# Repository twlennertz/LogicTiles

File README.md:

<h2>Digital Logic Tile Board Project</h2>

Spring 2017 Senior Project

Cal Poly CPE Department

Authors: Tristan Lennertz & Andrew Wheeler

Implemented for the MSP430 Family

<h3>Please see Project Report for detailed information on this project</h3>

main: The main state machine loop, inits, terminal interface and commands, and ISRs

tiles: Pertains to addressing, selecting, reading, and determining the types of the tiles on the board

graph: Involves the creation and traversal of the graph that underlies and represents the digital circuit

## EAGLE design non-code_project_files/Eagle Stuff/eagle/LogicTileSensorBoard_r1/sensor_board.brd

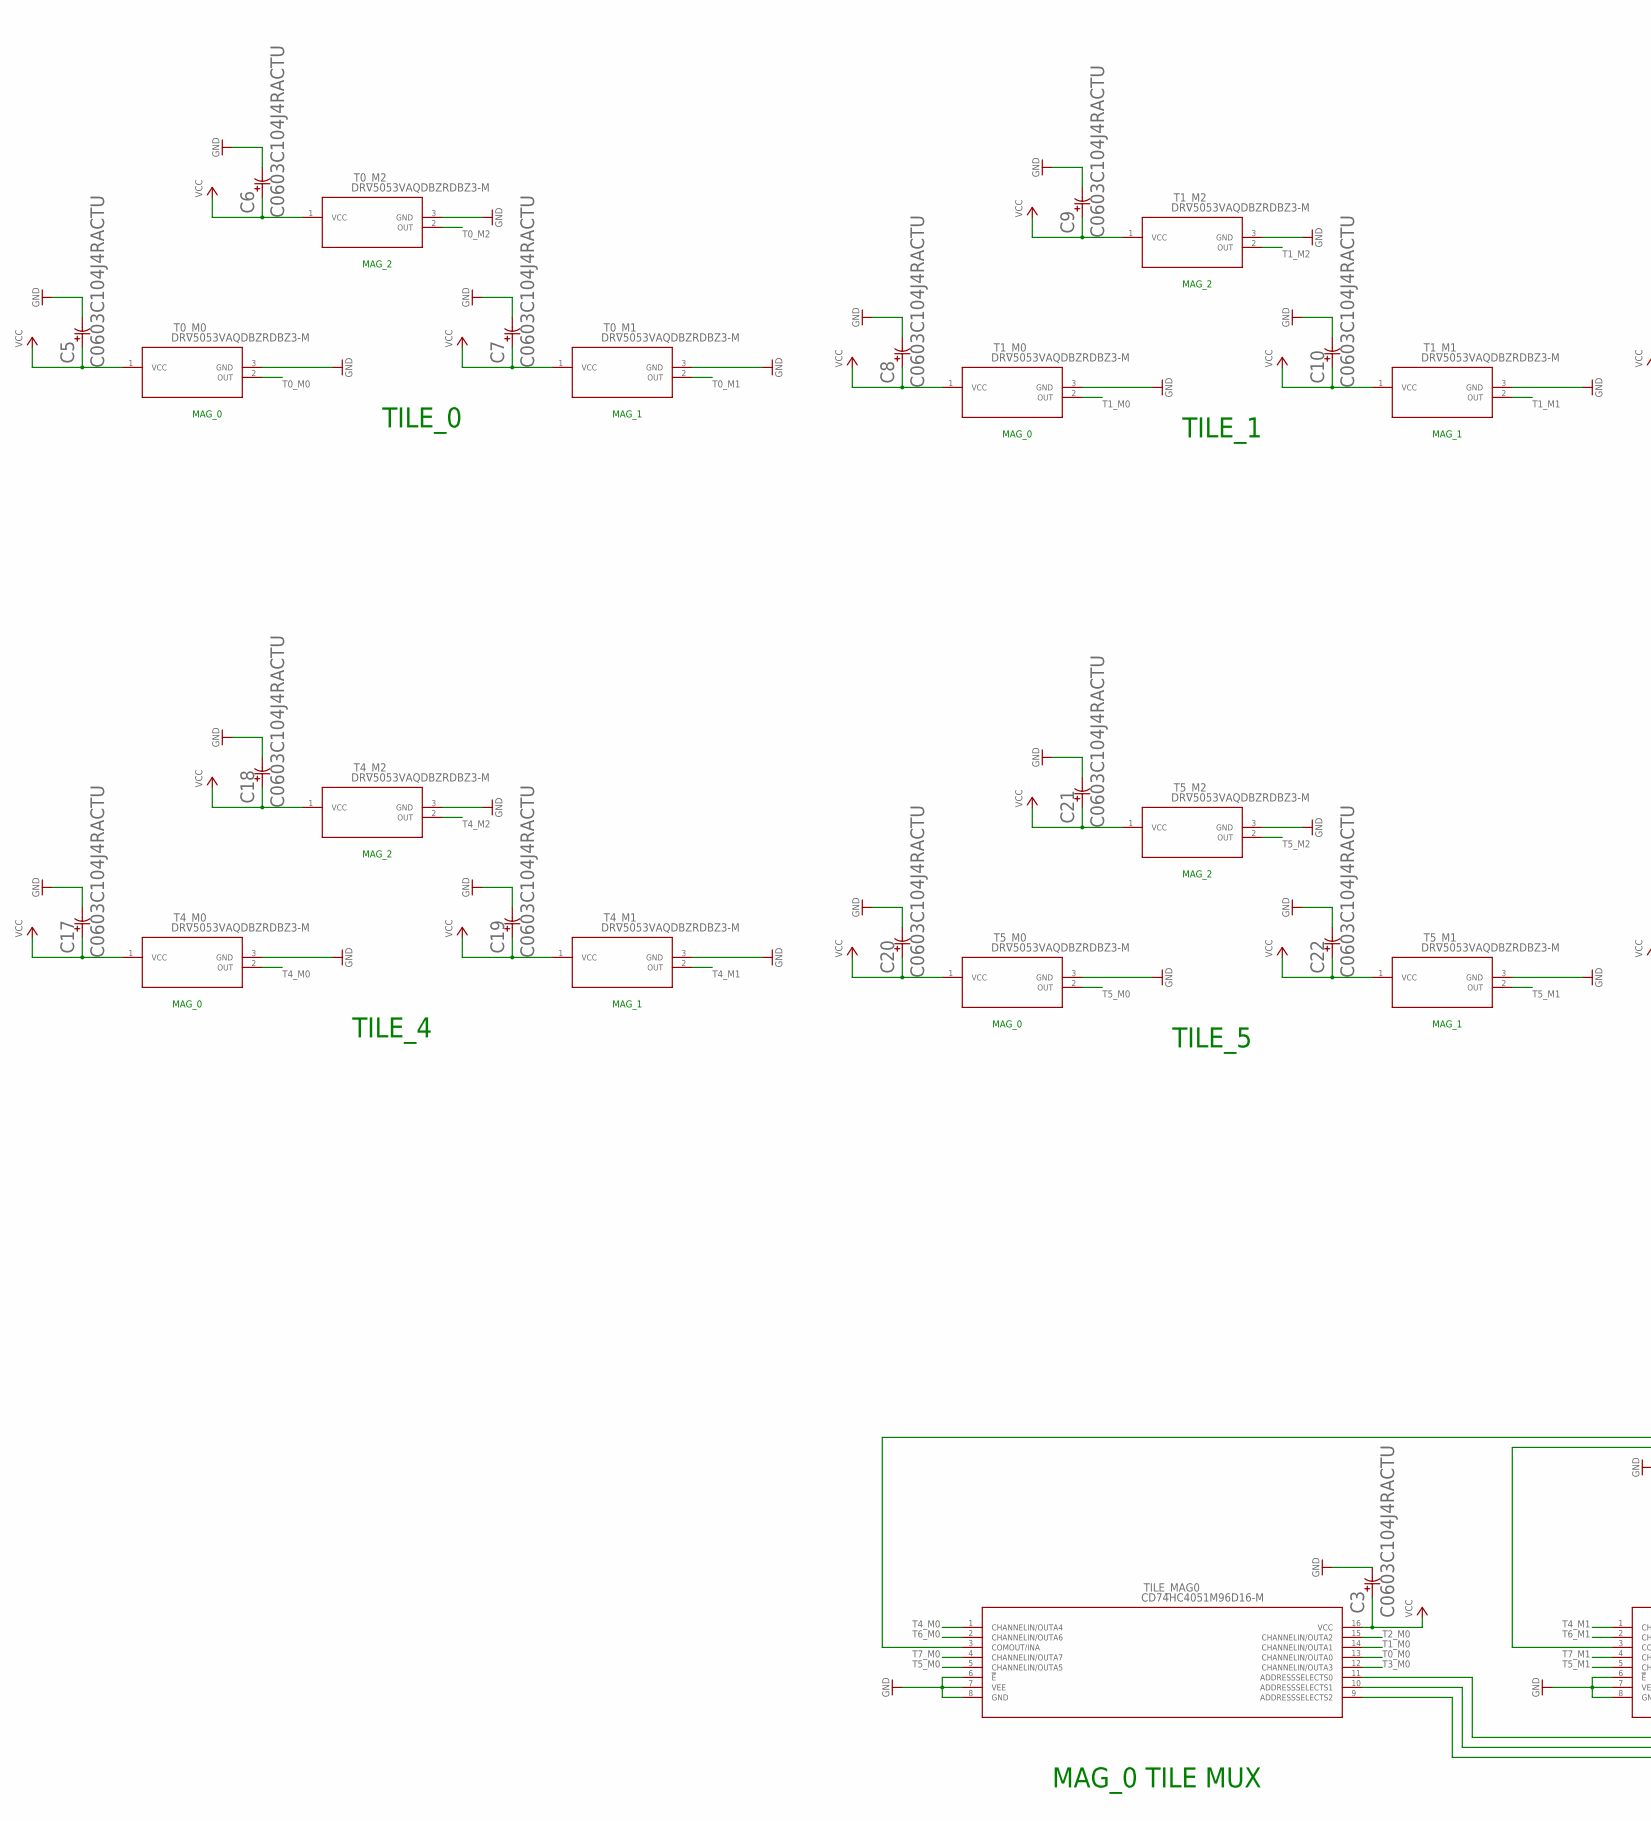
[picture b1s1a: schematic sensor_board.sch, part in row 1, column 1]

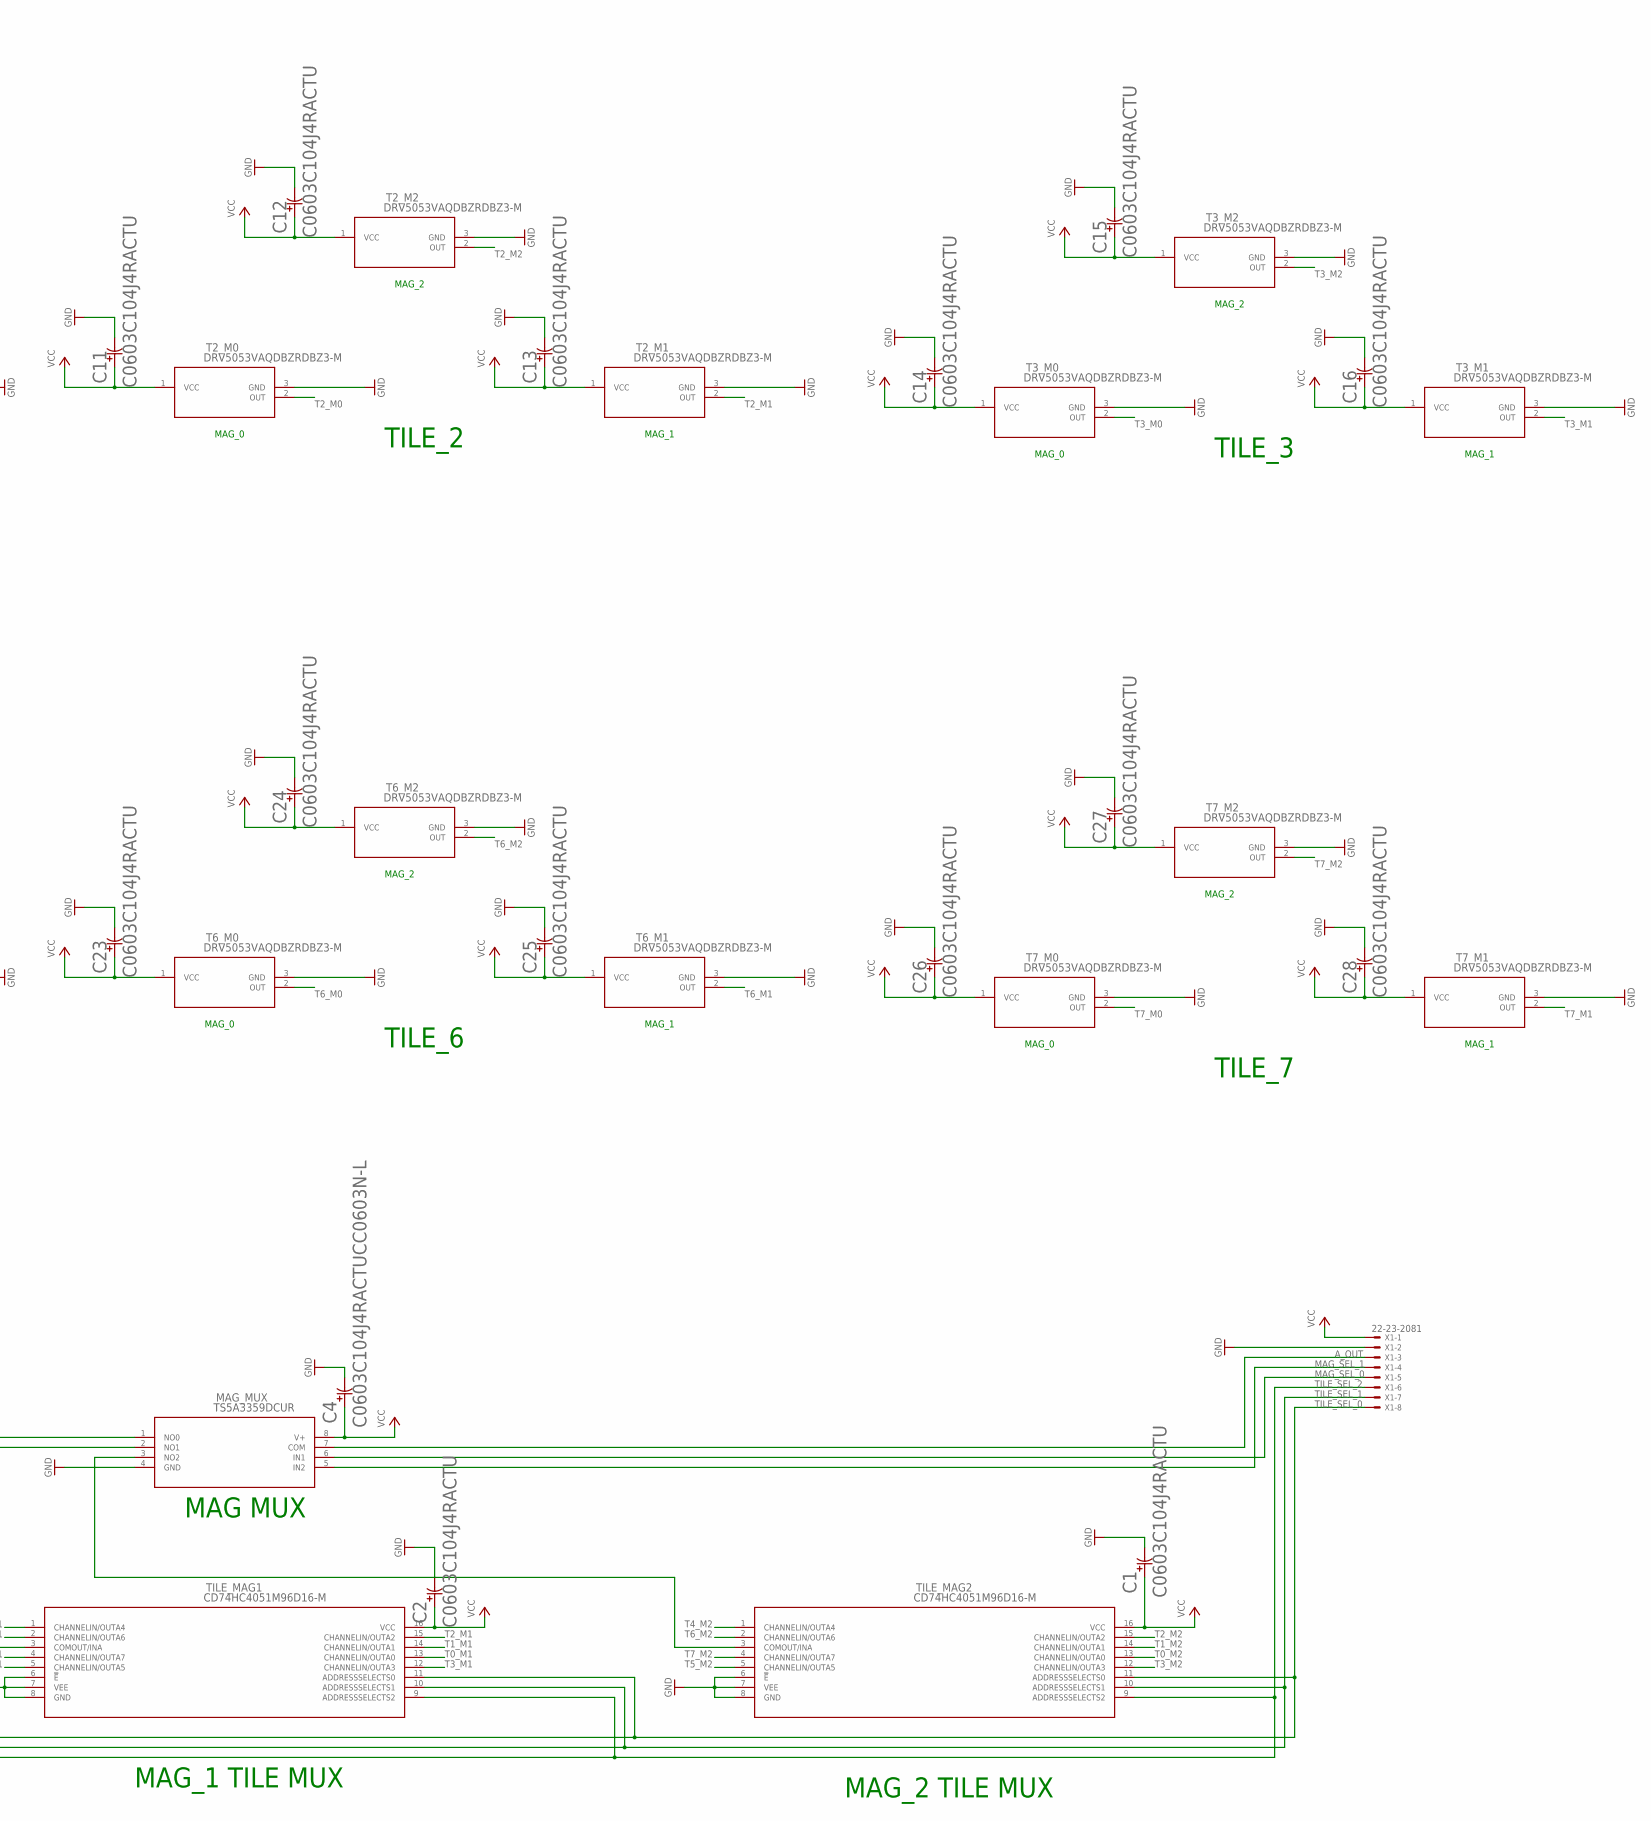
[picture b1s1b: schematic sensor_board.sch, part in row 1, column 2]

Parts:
C1, C2, C3, C5, C6, C7, C8, C9, C10, C11, C12, C13, C14, C15, C16, C17, C18, C19, C20, C21, C22, C23, C24, C25, C26, C27, C28: C0603C104J4RACTU; CC0603N
C4: C0603C104J4RACTUCC0603N-L; CC0603N-L
MAG_MUX: TS5A3359DCUR; DCU8
T0_M0, T0_M1, T0_M2, T1_M0, T1_M1, T1_M2, T2_M0, T2_M1, T2_M2, T3_M0, T3_M1, T3_M2, T4_M0, T4_M1, T4_M2, T5_M0, T5_M1, T5_M2, T6_M0, T6_M1, T6_M2, T7_M0, T7_M1, T7_M2: DRV5053VAQDBZRDBZ3-M; DBZ3-M
TILE_MAG0, TILE_MAG1, TILE_MAG2: CD74HC4051M96D16-M; D16-M
X1: 22-23-2081

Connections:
A_OUT: MAG_MUX.7 (COM), X1.3
GND: C1.2 (22), C2.2 (22), C3.2 (22), C4.2 (22), C5.2 (22), C6.2 (22), C7.2 (22), C8.2 (22), C9.2 (22), C10.2 (22), C11.2 (22), C12.2 (22), C13.2 (22), C14.2 (22), C15.2 (22), C16.2 (22), C17.2 (22), C18.2 (22), C19.2 (22), C20.2 (22), C21.2 (22), C22.2 (22), C23.2 (22), C24.2 (22), C25.2 (22), C26.2 (22), C27.2 (22), C28.2 (22), MAG_MUX.4 (GND), T0_M0.3 (GND), T0_M1.3 (GND), T0_M2.3 (GND), T1_M0.3 (GND), T1_M1.3 (GND), T1_M2.3 (GND), T2_M0.3 (GND), T2_M1.3 (GND), T2_M2.3 (GND), T3_M0.3 (GND), T3_M1.3 (GND), T3_M2.3 (GND), T4_M0.3 (GND), T4_M1.3 (GND), T4_M2.3 (GND), T5_M0.3 (GND), T5_M1.3 (GND), T5_M2.3 (GND), T6_M0.3 (GND), T6_M1.3 (GND), T6_M2.3 (GND), T7_M0.3 (GND), T7_M1.3 (GND), T7_M2.3 (GND), TILE_MAG0.6 (!E), TILE_MAG0.7 (VEE), TILE_MAG0.8 (GND), TILE_MAG1.6 (!E), TILE_MAG1.7 (VEE), TILE_MAG1.8 (GND), TILE_MAG2.6 (!E), TILE_MAG2.7 (VEE), TILE_MAG2.8 (GND), X1.2
MAG_SEL_0: MAG_MUX.6 (IN1), X1.5
MAG_SEL_1: MAG_MUX.5 (IN2), X1.4
unnamed: MAG_MUX.1 (NO0), TILE_MAG0.3 (COMOUT/INA)
unnamed: MAG_MUX.2 (NO1), TILE_MAG1.3 (COMOUT/INA)
unnamed: MAG_MUX.3 (NO2), TILE_MAG2.3 (COMOUT/INA)
T0_M0: T0_M0.2 (OUT), TILE_MAG0.13 (CHANNELIN/OUTA0)
T0_M1: T0_M1.2 (OUT), TILE_MAG1.13 (CHANNELIN/OUTA0)
T0_M2: T0_M2.2 (OUT), TILE_MAG2.13 (CHANNELIN/OUTA0)
T1_M0: T1_M0.2 (OUT), TILE_MAG0.14 (CHANNELIN/OUTA1)
T1_M1: T1_M1.2 (OUT), TILE_MAG1.14 (CHANNELIN/OUTA1)
T1_M2: T1_M2.2 (OUT), TILE_MAG2.14 (CHANNELIN/OUTA1)
T2_M0: T2_M0.2 (OUT), TILE_MAG0.15 (CHANNELIN/OUTA2)
T2_M1: T2_M1.2 (OUT), TILE_MAG1.15 (CHANNELIN/OUTA2)
T2_M2: T2_M2.2 (OUT), TILE_MAG2.15 (CHANNELIN/OUTA2)
T3_M0: T3_M0.2 (OUT), TILE_MAG0.12 (CHANNELIN/OUTA3)
T3_M1: T3_M1.2 (OUT), TILE_MAG1.12 (CHANNELIN/OUTA3)
T3_M2: T3_M2.2 (OUT), TILE_MAG2.12 (CHANNELIN/OUTA3)
T4_M0: T4_M0.2 (OUT), TILE_MAG0.1 (CHANNELIN/OUTA4)
T4_M1: T4_M1.2 (OUT), TILE_MAG1.1 (CHANNELIN/OUTA4)
T4_M2: T4_M2.2 (OUT), TILE_MAG2.1 (CHANNELIN/OUTA4)
T5_M0: T5_M0.2 (OUT), TILE_MAG0.5 (CHANNELIN/OUTA5)
T5_M1: T5_M1.2 (OUT), TILE_MAG1.5 (CHANNELIN/OUTA5)
T5_M2: T5_M2.2 (OUT), TILE_MAG2.5 (CHANNELIN/OUTA5)
T6_M0: T6_M0.2 (OUT), TILE_MAG0.2 (CHANNELIN/OUTA6)
T6_M1: T6_M1.2 (OUT), TILE_MAG1.2 (CHANNELIN/OUTA6)
T6_M2: T6_M2.2 (OUT), TILE_MAG2.2 (CHANNELIN/OUTA6)
T7_M0: T7_M0.2 (OUT), TILE_MAG0.4 (CHANNELIN/OUTA7)
T7_M1: T7_M1.2 (OUT), TILE_MAG1.4 (CHANNELIN/OUTA7)
T7_M2: T7_M2.2 (OUT), TILE_MAG2.4 (CHANNELIN/OUTA7)
TILE_SEL_0: TILE_MAG0.11 (ADDRESSSELECTS0), TILE_MAG1.11 (ADDRESSSELECTS0), TILE_MAG2.11 (ADDRESSSELECTS0), X1.8
TILE_SEL_1: TILE_MAG0.10 (ADDRESSSELECTS1), TILE_MAG1.10 (ADDRESSSELECTS1), TILE_MAG2.10 (ADDRESSSELECTS1), X1.7
TILE_SEL_2: TILE_MAG0.9 (ADDRESSSELECTS2), TILE_MAG1.9 (ADDRESSSELECTS2), TILE_MAG2.9 (ADDRESSSELECTS2), X1.6
VCC: C1.1 (11), C2.1 (11), C3.1 (11), C4.1 (11), C5.1 (11), C6.1 (11), C7.1 (11), C8.1 (11), C9.1 (11), C10.1 (11), C11.1 (11), C12.1 (11), C13.1 (11), C14.1 (11), C15.1 (11), C16.1 (11), C17.1 (11), C18.1 (11), C19.1 (11), C20.1 (11), C21.1 (11), C22.1 (11), C23.1 (11), C24.1 (11), C25.1 (11), C26.1 (11), C27.1 (11), C28.1 (11), MAG_MUX.8 (V+), T0_M0.1 (VCC), T0_M1.1 (VCC), T0_M2.1 (VCC), T1_M0.1 (VCC), T1_M1.1 (VCC), T1_M2.1 (VCC), T2_M0.1 (VCC), T2_M1.1 (VCC), T2_M2.1 (VCC), T3_M0.1 (VCC), T3_M1.1 (VCC), T3_M2.1 (VCC), T4_M0.1 (VCC), T4_M1.1 (VCC), T4_M2.1 (VCC), T5_M0.1 (VCC), T5_M1.1 (VCC), T5_M2.1 (VCC), T6_M0.1 (VCC), T6_M1.1 (VCC), T6_M2.1 (VCC), T7_M0.1 (VCC), T7_M1.1 (VCC), T7_M2.1 (VCC), TILE_MAG0.16 (VCC), TILE_MAG1.16 (VCC), TILE_MAG2.16 (VCC), X1.1

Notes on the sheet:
TILE_0
TILE_1
TILE_2
TILE_3
TILE_4
TILE_5
TILE_6
TILE_7
MAG_0
MAG_2
MAG_1
MAG_0 TILE MUX
MAG_1 TILE MUX
MAG_2 TILE MUX
MAG MUX

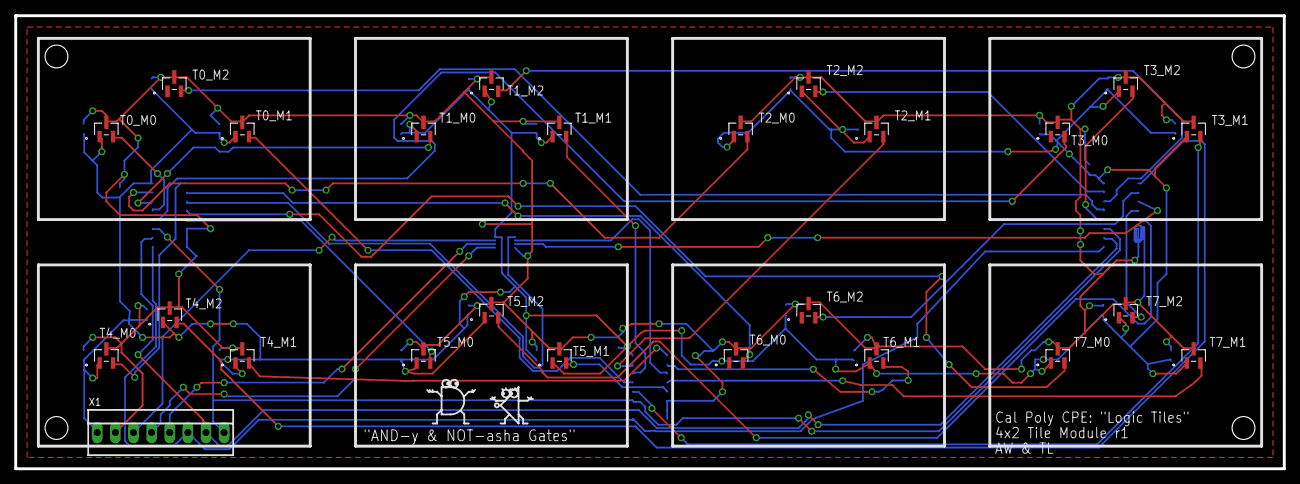
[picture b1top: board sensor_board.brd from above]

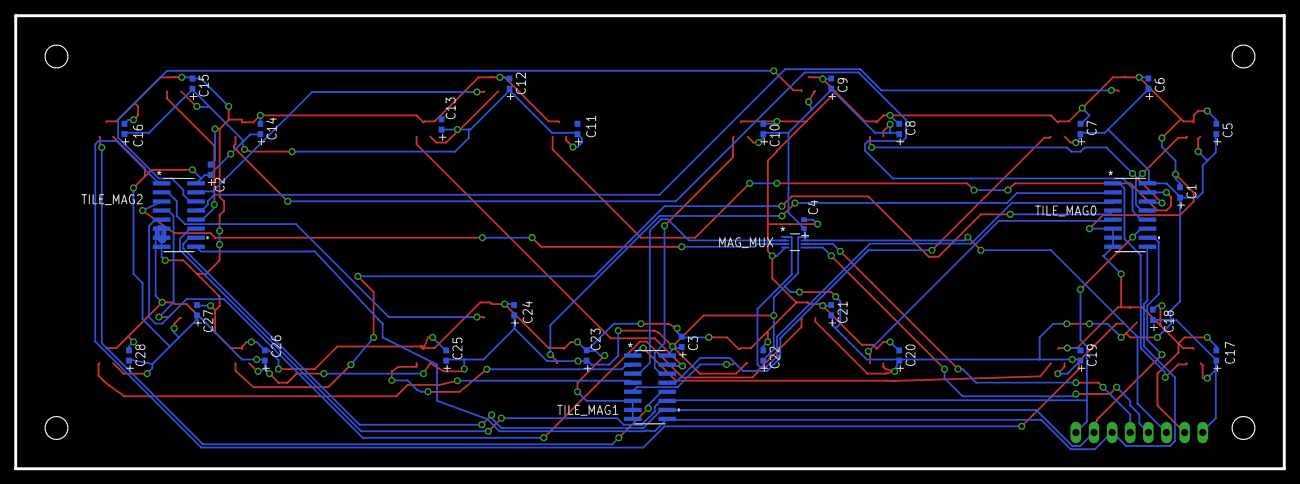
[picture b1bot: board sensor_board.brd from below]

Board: 2 copper layers, 177.8 x 63.5 mm, 57 parts (32 on the bottom side), 35 nets.

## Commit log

2017-05-14 :lollipop: Added .gitattributes & .gitignore files
2017-05-14 First Push
    Blinking LED
2017-05-14 FFFUUUUCK
2017-05-14 OH SHIT
    TEST THIS SHIT
2017-05-14 CHANGE 2
    TEST FROM LAPTOP
2017-05-15 Beginning
    First demo 5/14
2017-05-15 Error?
    Where is it?
2017-05-15 work
2017-05-15 End of Day 5/14
    Can Cycle through all magnets and tiles and get a good read.
2017-05-17 Mr. Clean
    Cleaned up some code, added skeletons for helper functions, and added
    comments to all functions. Also, added functionality for a USART
    connection. This will add some help with debugging. It has not been
    tested however.
2017-05-20 UART Enabled
    Now we got UART!
2017-05-20 State Machine Skeleton
    Added skeleton of state machine and moved around initializations a bit.
2017-05-20 Polling Tiles Framework
    Added the flow of polling all the tiles. Still needs specific
    implementations on pins and magnet read value ranges.
2017-05-20 Good Parse
    We now have a pretty robust Parse going now. Commands can be read in an
    will be executed after the enter key has been pressed.
2017-05-27 tile.c & more!
    Implemented the select functions, moved stuff around (mostly to tile.c),
    added lots of documentation and portability options.
2017-05-27 Minor cleanup
2017-05-29 tileTypes all added in determineType()
2017-05-29 ERRMAGERRRHD. GRERPHS.
    Added graph.c/h, with backbone for building circuit graph. Also updated
    TileState structure to have pointers to potential nodes on a tile's
    bottom, top, right, and left sides.
2017-05-29 Quick Struct Fix
    Yup that's it.
2017-05-29 Using your Nodal!
    Implemented methods of adding nodes to our graph.c. When a new tile is
    placed on the board, nodes are added to each of the end points of a tile
    and are used to connect various tiles together. Each node connect two
    tiles at either a vertial or horizontal connection.
2017-06-01 Fixed N1 S2 Defines, Cleaned up Main.c
2017-06-01 Read ADC
    Added function to print read ADC values
2017-06-01 stuff
2017-06-02 Graph Building
    Should be correct (if not slightly confusing)
2017-06-02 Recursive Graph Function
2017-06-02 ERMAGERHD, RECURSHHUN
2017-06-02 Finished Up The Graph Recursion
    And also fixed a few graph building things. Hopefully.
2017-06-02 Lots of Debugging Code
2017-06-02 dick
2017-06-04 Cleaned up / added debugging code
2017-06-04 Added TX Interrupt functionality with a ring buffer
2017-06-05 Got into a good debugging place
2017-06-05 Minor Debugging Changes
2017-06-05 stufff
2017-06-06 Most things fixed. New tiles might do it
2017-06-07 Proper (enough) ranges
2017-06-09 DEBUGGING RUN
2017-06-10 Final Cleanup
2017-06-10 Project Files Added
